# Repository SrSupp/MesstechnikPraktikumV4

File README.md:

Author: Sven Suppelt		      
Date: 31.03.2023

# Messtechnik Praktikum: Grundlagen der Medizinrobotik
Das ist das Github zum V4 des [Messtechnik-Praktikums](https://www.etit.tu-darmstadt.de/must/teaching_must/measurement_technology_lab_must/index.de.jsp). Hier ist alles zum Endeffektor, zu Ros, die Vorbereitungsaufgabe und ein Auswerteskript enthalten.
Weitere Infos finden Sie im Moodle Forum des Praktikums.

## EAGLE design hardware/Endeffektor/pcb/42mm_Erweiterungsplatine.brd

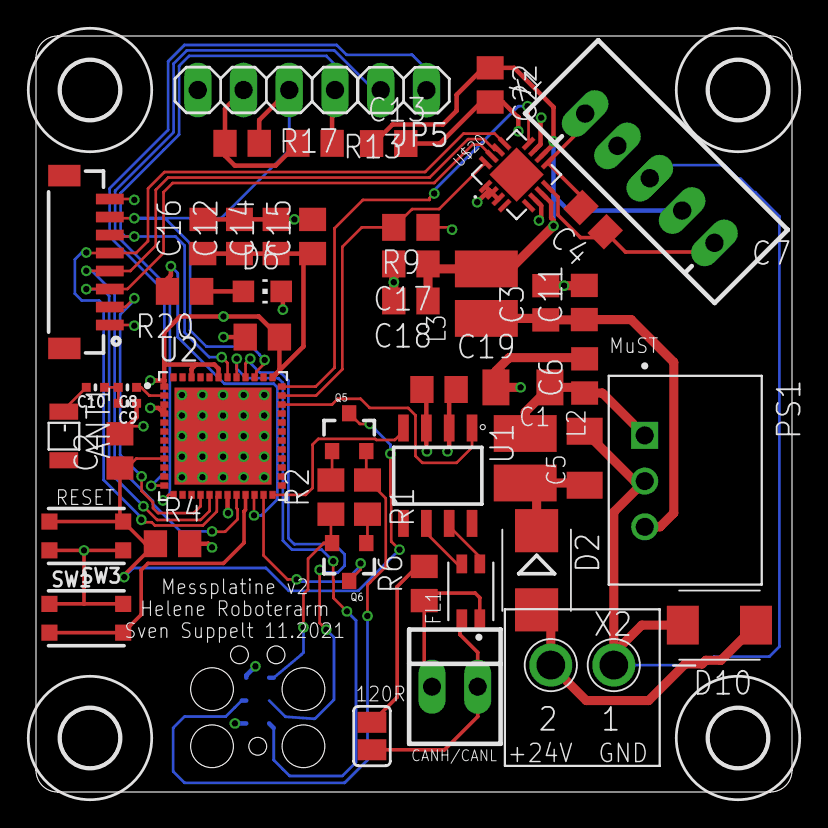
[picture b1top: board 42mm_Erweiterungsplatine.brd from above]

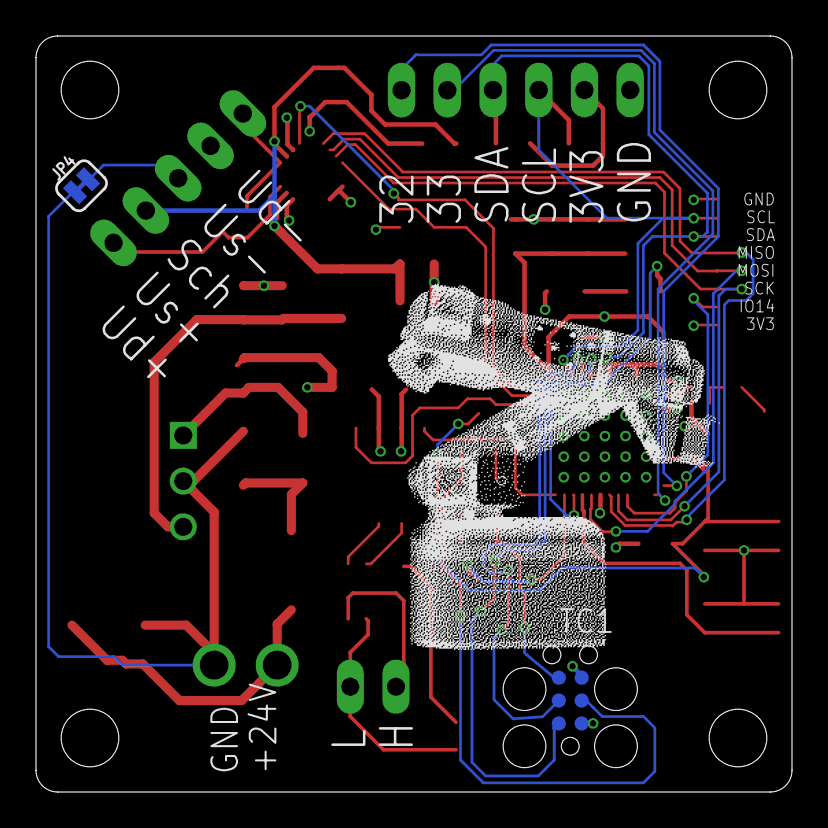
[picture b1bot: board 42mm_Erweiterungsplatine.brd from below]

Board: 4 copper layers, 42.0 x 42.0 mm, 56 parts (2 on the bottom side), 40 nets.

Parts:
ANT1: 2450AT18B100E; ANT_2450AT18B100E
C1, C5: C1206K
C2: 1u; C0805
C3: 47u; C0805
C4: 10n_C0G; C0805
C6: 4u7; C0805
C7, C11, C19, C22: 100n; C0805
C8: 1.2pF; _0402MP
C9: 2.7nH; _0402MP
C10: 3.3nH; _0402MP
C12, C13, C14, C15, C16: 10u; C0805
C17, C18: 22u; C0805
D2: Schottky; SMB
D6: RE; CHIP-LED0805
D10: SMBJ30AQ-13-F; SMBJ
FL1: DLW32SH220XK2L; FIL_DLW32SH110XK2L
J2: BM08B-SRSS-TB
JP1: 1X04
JP4: JUMPER-SMT_2_NC_TRACE_SILK; SMT-JUMPER_2_NC_TRACE_SILK
JP5: PINHD-1X2; 1X02
L2, L3: RLS-567-R; IND_RLS-567-R
PS1: R-78E3.3-0.5; CONV_R-78E3.3-0.5
Q5, Q6: BC817; SOT23-3
R1, R2, R20: 1k; R0805
R4, R9, R13, R17: 10k; R0805
R6: 120R; R0805
SJ9: SJ
SW1, SW3: KMR2; BTN_KMR2_4.6X2.8
TC1: TC2030-IDC
U1: SN65HVD232; SOIC127P600X175-8N
U2: ESP32-PICO-D4; PQFN50P700X700X104-49N
U$1, U$2, U$3, U$4: 3,2
U$20: ADS1220IRVAR; QFN50P350X350X100-17N214X214
X1: JST-XH-05-PIN-LONG-PAD; JST-XH-05-PACKAGE-LONG-PAD
X2: TYP183_2PIN183_2PIN; TYP183_FT_2PIN
X6: 22-23-2021

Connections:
+3V3: C3.1, C7.1, C11.1, C12.1, C14.1, C15.1, C16.1, C19.1, J2.1, JP1.2, L3.1, PS1.3, R4.2, R9.1, R13.2, R17.2, TC1.1, U1.3, U2.1, U2.3, U2.4, U2.19, U2.37, U2.43, U2.46, U$20.11
+24V: D2.A, D10.C, X2.2
ADC1_AIN0: C4.2, U$20.9, X1.1
ADC1_AIN1: C4.1, U$20.8, X1.5
AVDD: C13.1, C17.1, C18.1, C22.1, L3.2, U$20.7, U$20.10, X1.4
CANH: FL1.1, R6.1, X6.1
CANL: FL1.4, SJ9.1, X6.2
DTR: Q6.2, R2.1, TC1.6
EN: C2.1, Q5.3, R4.1, SW3.B, SW3.B', U2.9
GND: C1.2, C2.2, C3.2, C5.2, C6.2, C7.2, C9.1, C11.2, C12.2, C13.2, C14.2, C15.2, C16.2, C17.2, C18.2, C19.2, C22.2, D6.C, D10.A, J2.8, JP1.1, JP4.1, PS1.2, SW1.A, SW1.A', SW3.A, SW3.A', TC1.5, U1.2, U2.49, U$20.1, U$20.2, U$20.3, U$20.6, X1.2, X2.1
GPIO0: Q6.3, U2.23
GPIO2: R20.2, U2.22
IO4_CANRX: U1.4, U2.24
IO5_CANTX: U1.1, U2.34
IO14_CSN_EXT: J2.2, U2.16
IO15_BUTTON: SW1.B, SW1.B', U2.21
IO18_CS_ADC1: R9.2, U2.35, U$20.16
IO23_DRDY_ADC1: U2.36, U$20.12
IO32_OUT: JP5.1, U2.12
IO33_OUT: JP5.2, U2.13
LNA_IN: C8.1, U2.2
MISO: J2.5, U2.18, U$20.13
MOSI: J2.4, U2.20, U$20.14
unnamed: C8.2, C9.2, C10.1
unnamed: ANT1.1, C10.2
unnamed: C5.1, D2.C, L2.2
unnamed: D6.A, R20.1
unnamed: C1.1, C6.1, L2.1, PS1.1
unnamed: JP4.2, X1.3
unnamed: FL1.2, U1.7
unnamed: FL1.3, U1.6
unnamed: Q5.1, R2.2
unnamed: Q6.1, R1.2
unnamed: R6.2, SJ9.2
RTS: Q5.2, R1.1, TC1.3
RXD0: TC1.4, U2.40
SCK: J2.3, U2.17, U$20.15
SCL: J2.7, JP1.3, R17.1, U2.39
SDA: J2.6, JP1.4, R13.1, U2.42
TXD0: TC1.2, U2.41

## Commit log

2022-02-22 Initial setup, src is from Yannick
2022-02-22 Added PCB, code and CAD model of the end effector
2022-02-25 Der reale Roboterarm wird mit einem anderen PC verbunden. Die vorbereitungen werden mit diesem Commit getätigt
2022-04-20 Various changes
2022-05-06 Added the latest changes
2022-05-06 Working on finalizing
2022-05-06 Progress is made
2022-05-06 more progress
2022-05-06 Progress was made
2022-05-06 Ich gehe jetzt Eis essen
2022-05-16 Modified Edeffektor
2022-05-16 Added the tumor
2022-05-17 finished workspace
2022-05-18 Hinzufügen der Vorbereitungsaufgabe
2022-05-23 Update Python stuff
2022-05-23 Methoden haben neue Namen
2022-05-28 improved the launch files
2022-05-28 Reset
2022-05-28 Reset2
2022-05-28 Reset3
2022-06-13 Create LICENSE
2022-06-21 Update Endeffektor
2022-06-27 Added libs
2022-06-29 Neue Rohmessdaten
2022-06-30 Update install_icons.sh
    sudo apt-get install octave
    sudo apt-get install octave-signal
    Muss nun manuell durchgeführt werden.
2022-07-06 Hintergrundbild
2022-07-06 External Update Script
2022-07-06 final
2022-07-06 Robot Upload
2022-07-06 Neues Hintergrundbild
2022-07-14 Ich habe Kommentare hinzugefügt
2024-05-06 Update update_script.sh
    Hintergrundbild weg
2024-06-14 Removed Old Background Picture

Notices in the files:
parts and their libraries:
microbuilder: This work is placed in the public domain, and may be freely used for commercial and non-commercial work with the following conditions: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
SparkFun-Connectors: Licensing: Creative Commons ShareAlike 4.0 International - https://creativecommons.org/licenses/by-sa/4.0
